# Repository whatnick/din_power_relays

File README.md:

# DIN Rail Format Energy Meter Base Board
## Power SMPS module
- 90v-240v AC input
- Isolated 5V output
- 600mA / 3W power rating

## Over-voltage protection/over-current protection
- 0.1A rated PTC fuse
- 300V rated TVS suppressors, x1 per-phase

## Isolation
- 5v DC-DC isolator to power metering module

## Power supply clean-up
- x2 1117 series LDO for generating 3.3v from 5V input to clean up SMPS noise

## Backup-power
- MCP73831 series floating Lipo battery charger for backup lipo battery

## AC Voltage Sampler
- x3 Voltage divider ladders with 880K + 1K total serial resistance

## AC current Sampler
- x4 2.4ohm current sense resistor based CT clamp inputs

## Relay Driver
- x4 optoisolated relay driver connectors, external power required to operate relays.

## Connectors
- 5.08mm spacing phoenix contact AC voltage connector
- Molex nanofit 2x4 type dense AC current clamp connectors

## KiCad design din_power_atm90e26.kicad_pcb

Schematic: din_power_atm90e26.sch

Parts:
C1, C2, C3: 33n; C_0603
C5, C6, C7, C8: 1uF; C_0603
F1: Polyfuse; C_Disc_D10.0mm_W2.5mm_P5.00mm
G1: LOGO; Whatnick_logo
J1: CONN_01X06; PhoenixContact_MC-G_06x5.08mm_Angled
J2: Conn_01x04; JST_SH_BM04B-SRSS-TB_1x04-1MP_P1.00mm_Vertical
J3, J5: CONN_01X08; Molex_NanoFit_2x04x2.50mm_Angled
J4: CONN_02X18; PCIE-36-SKT
L1: Ferrite_Bead_Small; L_1206
LOGO_OSHW1: Logo_Open_Hardware_Small; OSHW-Symbol_6.7x6mm_SilkScreen
R1, R2, R3, R4, R8, R9, R10, R11: 2.4R; R_0603
R5, R6, R7, R12, R13, R14, R15, R16, R17, R22, R23, R24: 220K; R_1206
R18: 330R; R_0603_1608Metric
R25, R26, R27: 1K; R_0603
RV1, RV2, RV3: Varistor; SMD-4032
SYM1: SYM_Flash_Small; Fsilk_HV
U1, U6, U7, U8: LTV-356T; SO-4_4.4x3.6mm_P2.54mm
U2: L78L33_SOT89; SOT-89-3
U3: L78L05_SOT89; SOT-89-3
U4: Hi-Link_SMPS; HKLPM01
U5: dc-dc; SIP4

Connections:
+3.3V_ISO: C8.1, J4.8, U3.1 (OUT)
+3V3: C7.1, J4.32, U2.1 (OUT)
+5V: C6.1, J4.34, U2.3 (IN), U4.4, U5.2
+5V_ISO: C5.1, J4.9, U3.3 (IN), U5.4
/UN_IN: F1.1, U4.2
/ua_1: R5.1, R12.2
/ua_2: R12.1, R15.2
/ua_3: R15.1, R22.2
/ub_1: R6.1, R13.2
/ub_2: R13.1, R16.2
/ub_3: R16.1, R23.2
/uc_1: R7.1, R14.2
/uc_2: R14.1, R17.2
/uc_3: R17.1, R24.2
GNDA: C1.2, C2.2, C3.2, C5.2, C8.2, J4.7, L1.1, R1.1, R2.2, R3.1, R4.2, R8.1, R9.2, R10.1, R11.2, R25.1, R26.1, R27.1, U3.2 (GND), U5.3
GNDPWR: C6.2, C7.2, J4.36, R18.2, U2.2 (GND), U4.3, U5.1
IA1+: J4.11, J5.1, R1.2
IA1-: J4.13, J5.2, R2.1
IA2+: J4.27
IA2-: J4.29
IB1+: J4.15, J5.3, R8.2
IB1-: J4.17, J5.4, R9.1
IB2+: J4.31
IB2-: J4.33
IC1+: J4.19, J5.5, R3.2
IC1-: J4.21, J5.6, R4.1
IC2+: J4.35
IC2-: J4.2
IN1+: J4.23, J5.7, R10.2
IN1-: J4.25, J5.8, R11.1
IN2+: J4.4
IN2-: J4.6
LED_H1: J2.1, U1.1
LED_H2: J2.2, U6.1
LED_H3: J2.3, U7.1
LED_H4: J2.4, U8.1
LED_L: R18.1, U1.2, U6.2, U7.2, U8.2
RE1_H: J3.1, U1.4
RE1_L: J3.2, U1.3
RE2_H: J3.3, U6.4
RE2_L: J3.4, U6.3
RE3_H: J3.5, U7.4
RE3_L: J3.6, U7.3
RE4_H: J3.7, U8.4
RE4_L: J3.8, U8.3
UA: J1.1, R5.2, RV1.2
UA_SAMP: C3.1, J4.5, R22.1, R25.2
UB: J1.3, R6.2, RV2.2
UB_SAMP: C1.1, J4.3, R23.1, R26.2
UC: J1.5, R7.2, RV3.2, U4.1
UC_SAMP: C2.1, J4.1, R24.1, R27.2
UN: F1.2, J1.6, L1.2, RV1.1, RV2.1, RV3.1
VBAT: J4.30

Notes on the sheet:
Power Systems (5V)
Voltage Sampling
Current Sampling
CT Input
Connector for Metering/Processor boards - Supplies IV samples and +5V power with/without isolation
Optional N-CT1
Power Systems - dual 3.3v LDO
Optocoupler driver

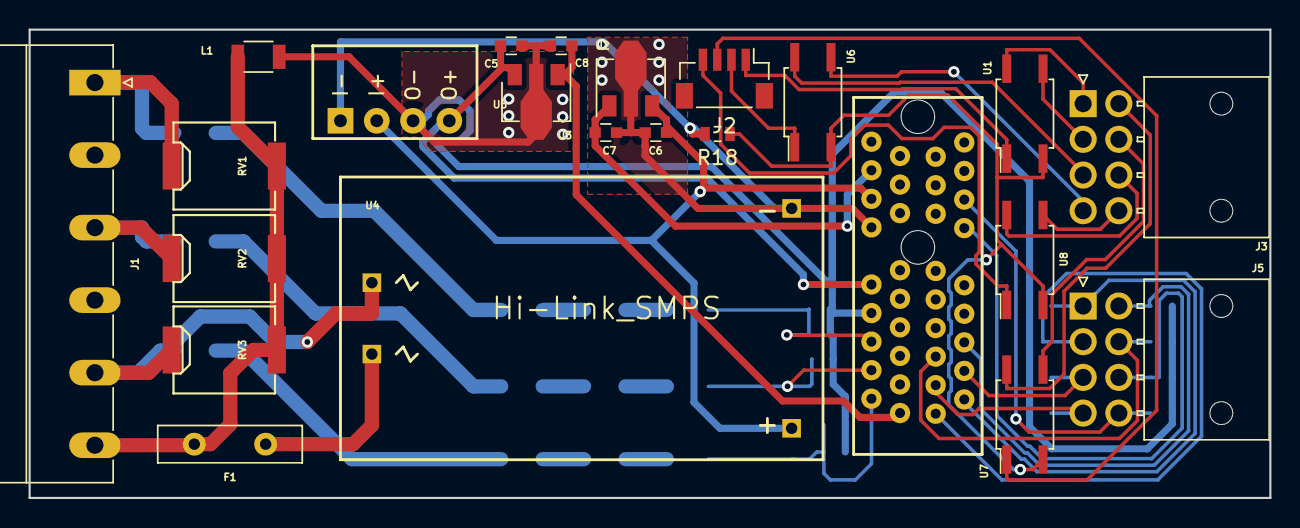
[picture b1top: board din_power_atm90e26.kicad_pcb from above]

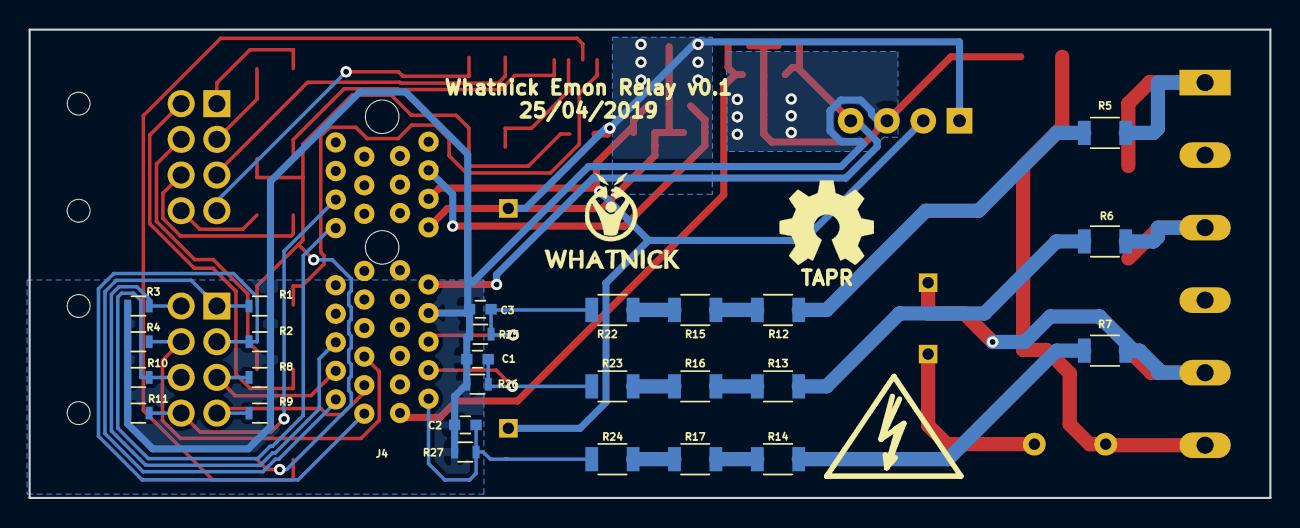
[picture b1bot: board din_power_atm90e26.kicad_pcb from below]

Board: 2 copper layers, 86.9 x 32.8 mm, 52 parts (30 on the bottom side), 44 nets.

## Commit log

2019-02-18 Added notes in README.md for relay driver
2019-02-18 Begin migration to relay drivers
2019-03-03 Updates links to new KiCAD libraries
2019-04-24 Ripped out routing and added individual optos
2019-05-01 Added routing for Opto-driver based PCB
2019-05-03 Finalize BOM and Gerbers
2019-05-03 New BOM and parts postions
